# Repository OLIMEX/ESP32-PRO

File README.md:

# ESP32-PRO
Open-source hardware ESP32 IoT board with 4MB external RAM, 4MB external flash, LiPo charger, USB-OTG, external crypto engine option. The board uses PIC32 as USB-serial converter. 

Product page:

https://www.olimex.com/Products/IoT/ESP32/ESP32-PRO/open-source-hardware

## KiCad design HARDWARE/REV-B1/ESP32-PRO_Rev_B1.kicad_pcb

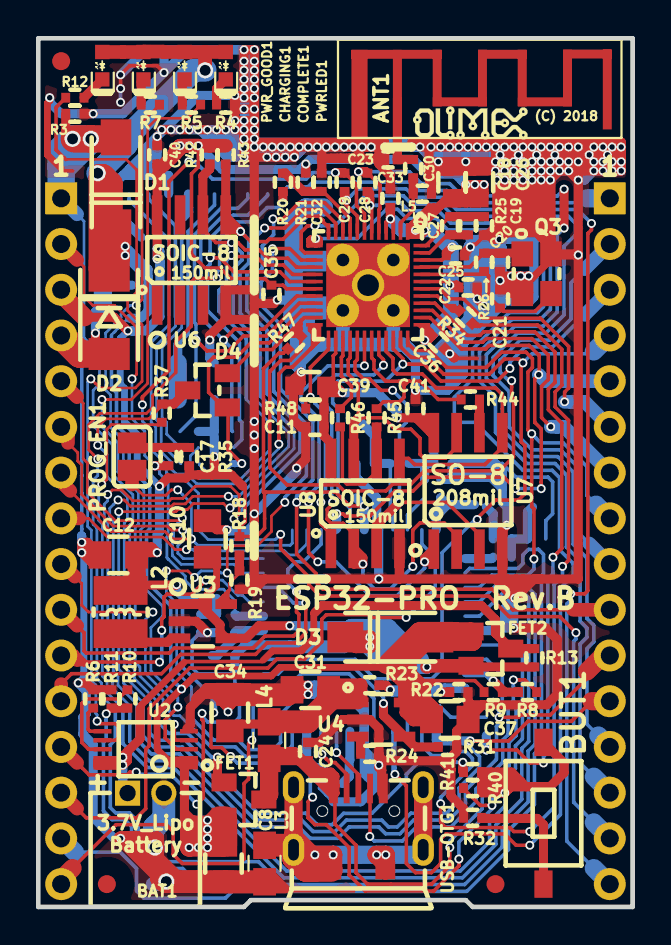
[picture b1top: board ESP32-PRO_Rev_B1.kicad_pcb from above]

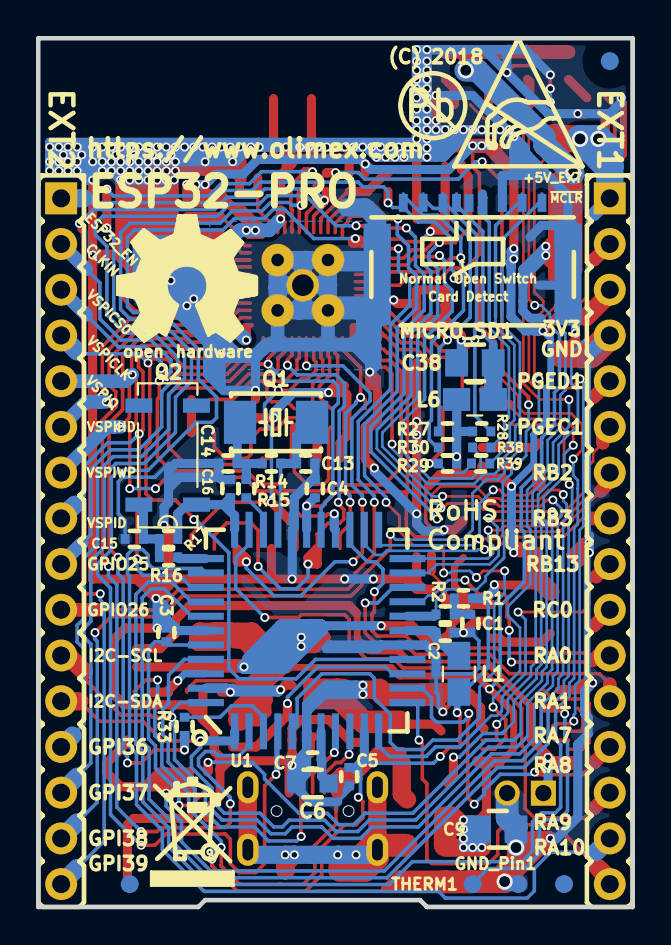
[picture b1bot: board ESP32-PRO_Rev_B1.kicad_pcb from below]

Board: 2 copper layers, 33.0 x 48.3 mm, 132 parts (40 on the bottom side), 104 nets.

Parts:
ANT1: WIFI_ANT; BT_Antenna_Inverted_1ANT_2GND
BAT1: DW02R; LIPO_BAT-CON2DW02R
BUT1: T1107A(6x3,8x2,5MM)
C1, C2, C3, C4, C5, C7, C11, C17, C22, C24, C32, C33, C35, C36, C41: 100nF/10V/10%/X5R/C0402; C_0402_5MIL_DWS
C6: 22uF/6.3V/20%/X5R/C0603; C_0603_5MIL_DWS
C8, C9, C10, C12, C31, C34, C37, C38: 47uF/6.3V/20%/X5R/C0805; C_0805_5MIL_DWS
C13, C14, C15, C16, C25: 33pF/50V/5%/COG/C0402; C_0402_5MIL_DWS
C18, C26, C39: 1uF/10V/10%/X5R/C0603; C_0603_5MIL_DWS
C19: 10nF/50V/10%/X7R/C0402; C_0402_5MIL_DWS
C20, C21: 22pF/50V/5%/COG/C0402; C_0402_5MIL_DWS
C23: 2.4pF/50V/±0.25pF/COG/C0402(Murata_Electronics/GR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; C_0402_5MIL_DWS
C27: 3.3nF/50V/10%/X7R/C0402; C_0402_5MIL_DWS
C28, C29: 270pF/50V/5%/COG/C0402; C_0402_5MIL_DWS
C30: 2.4nH/±0.1nH/220mA/300mR/L0402(Murata_Electronics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; C_0402_5MIL_DWS
C40: NA(100nF/10V/10%/X5R/C0402); C_0402_5MIL_DWS
CHARGING1: LED/YELLOW/0603; LED_0603_KA
COMPLETE1: LED/GREEN/0603; LED_0603_KA
D1, D3: 1N5822/SS34/SMA; SMA-KA
D2: SMBJ6.0A(DO-214AA); DO214AA_1(K)-2(A)
D4: BAT54C(SOT23-3); SOT23-3
EXT1, EXT2: NS(HN1x16); HN1x16
FET1, FET2: WPM2015-3/TR(SOT-23); SOT23
FID1, FID2, FID3, FID4, FID5, FID6: Fiducial; Fiducial1x3
GND_Pin1: TESTPAD; TESTPAD_40-ROUND
L1, L3, L4, L6: FB0805/600R/2A; L_0805_5MIL_DWS
L2: 2.2uH/1.5A/DCR<0.1R/CD32; CD32
L5: 4.7pF/50V/±0.1pF/COG/C0402(Murata_Electronics/GRM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; L_0402_5MIL_DWS
MICRO_SD1: TFC-9P-1.7H(ATFFS150A01BR016); uSD(TFC-9P-1.xH(ATFFS150A01BR016))
PROG_EN1: Unsoldered; SJ
PWRLED1: LED/RED/0603; LED_0603_KA
PWR_GOOD1: LED/RED/0603; LED_0603_KA
Q1: Q8.0MHz/20pF/20ppm/2P/5.0x3.2mm; HCX-4S_2Pins_5.0x3.2mm
Q2: Q32.768KHz/12.5pF/20ppm/2P/SMD_1206; MC306-HS
Q3: Q40.000MHz/12pF/10ppm/4P/3.2x2.5x0.70mm(Harmony_E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; TSX-3.2x2.5mm_GND(3)
R1, R3, R11, R21, R22, R31, R35, R40, R47, R48: 10k/R0402; R_0402_5MIL_DWS
R2, R10, R19: 1.1k/1%/R0402; R_0402_5MIL_DWS
R4, R5, R6, R7, R12, R15, R16, R27, R28, R29, R30, R42, R43: 2.2k/R0402; R_0402_5MIL_DWS
R8, R20, R32, R33, R34, R37, R39: 220R/R0402; R_0402_5MIL_DWS
R9: NA(220R/R0402); R_0402_5MIL_DWS
R13, R41, R45: NA/R0402; R_0402_5MIL_DWS
R14: 1M/1%/R0402; R_0402_5MIL_DWS
R17: NA(10M/1%/R0402); R_0402_5MIL_DWS
R18, R23: 4.99k/1%/R0402; R_0402_5MIL_DWS
R24: 13k/1%/R0402; R_0402_5MIL_DWS
R25: 20k/1%/R0402; R_0402_5MIL_DWS
R26: NA(1M/1%/R0402); R_0402_5MIL_DWS
R38, R44, R46: 22R/R0402; R_0402_5MIL_DWS
Ref**: Val**; LOGO_ANTISTATIC_1
THERM1: TESTPAD; TESTPAD_40-ROUND
U1: PIC32MX270F256DT-I/PT(TQFP44_10x10x1mm); TQFP44
U2: MCP73833(MSOP10); MSOP-10_Pitch-0.5mm_3.00x3.00x1.00mm
U3: SY8089AAAC(SOT23-5); SOT-23-5
U4: SY6280AAC(SOT23-5); SOT-23-5
U5: ESP32-D0WDQ6(QFN48_6x6mm); QFN48-6x6mm-OLIMEX_V2
U6: NA(ATECC508A-SSHDA-T(SOIC-8_150mil)); SOIC-8_150mil
U7: MX25U3235FM2I-10G(SOIC-8_208mil); SO-8_208mil
U8: LY68S3200SLT(SOIC-8_150mil); SOIC-8_150mil
USB-OTG1: MISB-SWMM-5AB-LF(USB-OTG_MICRO); USB-MICRO_MISB-SWMM-5B_LF

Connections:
+1V8: C11.2, C39.1, C41.2, R48.2, U5.26, U7.8, U8.8
+3V3: C3.1, C4.1, C5.1, C12.1, C18.1, C22.1, C25.1, C26.1, C33.1, C35.1, C36.1, C40.2, EXT1.3, L1.1, L2.2, L6.1, R1.2, R18.2, R21.1, R27.1, R28.1, R29.1, R30.1, R35.2, R40.2, R42.1, R43.1, R47.2, U1.10, U1.28, U1.40, U5.1, U5.3, U5.4, U5.19, U5.37, U5.43, U5.46, U6.8
+5V: C8.1, C9.1, C37.1, CHARGING1.2, COMPLETE1.2, D1.1, D2.1, D3.2, FET1.2, FET2.1, PWRLED1.2, PWR_GOOD1.2, R9.2, U2.1, U2.2, U4.5
+5V_EXT: D1.2, EXT1.1, FET1.1, R3.1
/+5V_USB-OTG: C24.1, FET1.3, L4.1, R8.2, USB-OTG1.1
/D_Com: D4.3, R37.2, R41.1
/ESP32_EN: EXT2.1, R20.1, U1.37
/ESP32_GPI35/BUT1: BUT1.1, R40.1, R41.2, U5.11
/ESP32_GPI36: C28.1, EXT2.13, U5.5
/ESP32_GPI37: C28.2, EXT2.14, U5.6
/ESP32_GPI38: C29.1, EXT2.15, U5.7
/ESP32_GPI39: C29.2, EXT2.16, U5.8
/ESP32_GPIO0/CLKIN: D4.2, EXT2.2, R47.1, U5.23
/ESP32_GPIO1/U0TXD: R34.2, U5.41
/ESP32_GPIO2/HS2_DATA0: D4.1, R29.2, R39.1, U5.22
/ESP32_GPIO3/U0RXD: R33.2, U5.40
/ESP32_GPIO4/HS2_DATA1: MICRO_SD1.8, U5.24
/ESP32_GPIO6/SD_CLK: R44.1, R45.1, U5.31
/ESP32_GPIO7/SD_DATA0: U5.32, U7.2, U8.2
/ESP32_GPIO8/SD_DATA1: U5.33, U7.5, U8.5
/ESP32_GPIO9/SD_DATA2: U5.28, U7.7, U8.7
/ESP32_GPIO10/SD_DATA3: U5.29, U7.3, U8.3
/ESP32_GPIO11/SD_CMD: U5.30, U7.1
/ESP32_GPIO12/HS2_DATA2: MICRO_SD1.1, R30.2, U5.18
/ESP32_GPIO13/HS2_DATA3: MICRO_SD1.2, R27.2, U5.20
/ESP32_GPIO14/HS2_CLK: R38.1, U5.17
/ESP32_GPIO15/HS2_CMD: MICRO_SD1.3, R28.2, U5.21
/ESP32_GPIO16/PSRAM_CS#: R48.1, U5.25, U8.1
/ESP32_GPIO17/PSRAM_SCLK: R46.1, U5.27
/ESP32_GPIO21/VSPIHD: EXT2.6, U5.42
/ESP32_GPIO22/VSPIWP: EXT2.7, U5.39
/ESP32_GPIO25: EXT2.9, U5.14
/ESP32_GPIO26: EXT2.10, U5.15
/RA0: EXT1.11, U1.19
/RA1: EXT1.12, U1.20
/RA2/OSC1: C13.1, Q1.1, R14.1, U1.30
/RA3/OSC2: R15.1, U1.31
/RA4/SOSCO: R16.1, U1.34
/RA7: EXT1.13, U1.13
/RA8: EXT1.14, U1.32
/RA9: EXT1.15, U1.35
/RA10: EXT1.16, U1.12
/RB0/PGED1: EXT1.5, U1.21
/RB1/PGEC1: EXT1.6, U1.22
/RB2: EXT1.7, PROG_EN1.1, U1.23
/RB3: EXT1.8, U1.24
/RB4/SOSCI: C16.1, Q2.2, R17.1, U1.33
/RB5/USB-OTG_ID: U1.41, USB-OTG1.4
/RB7/USB-OTG_FAULT: R22.1, R23.1, U1.43
/RB8/SCL1(ESP32_GPIO27/I2C-SCL): EXT2.11, R42.2, U1.44, U5.16, U6.6
/RB9/SDA1(ESP32_GPIO32/I2C-SDA): EXT2.12, R43.2, U1.1, U5.12, U6.5
/RB10/USB-OTG_D+: U1.8, USB-OTG1.3
/RB11/USB-OTG_D-: U1.9, USB-OTG1.2
/RB13: EXT1.9, U1.11
/RB14/USB-OTG_EN(VBUSON): R31.2, U1.14, U4.4
/RB15/SCK2(ESP32_GPIO18/VSPICLK): EXT2.4, U1.15, U5.35
/RC0: EXT1.10, U1.25
/RC1/SDO2(ESP32_GPIO19/VSPIQ): EXT2.5, U1.26, U5.38
/RC2/~SS2~(ESP32_GPIO5/VSPICS0): EXT2.3, U1.27, U5.34
/RC3/SDI2(ESP32_GPIO23/VSPID): EXT2.8, U1.36, U5.36
/RC5/~DTR~(ESP32_PGM): R37.1, U1.38
/RC6/U1RXD(ESP32_PGM): R34.1, U1.2
/RC7/U1TXD(ESP32_PGM): R33.1, U1.3
/RC8/U2RX(ESP32_GPIO33/U2TXD): U1.4, U5.13
/RC9/U2TX(ESP32_GPI34/U2RXD): U1.5, U5.10
/STAT1: R7.2, U2.3
/STAT2: R5.2, U2.4
/~MCLR: C17.1, EXT1.2, R2.2, U1.18
GND: ANT1.2, BAT1.2, C1.2, C2.2, C3.2, C4.2, C5.2, C6.2, C7.2, C8.2, C9.2, C10.1, C11.1, C12.2, C13.2, C14.2, C15.2, C16.2, C18.2, C19.2, C20.2, C21.2, C22.2, C23.1, C24.2, C25.2, C26.2, C31.2, C32.2, C33.2, C34.2, C35.2, C36.2, C37.2, C38.2, C39.2, C40.1, C41.1, D2.2, EXT1.4, GND_Pin1.1, L3.2, L5.2, MICRO_SD1.6, MICRO_SD1.CH1, Q3.3, R3.2, R4.2, R6.2, R11.2, R19.2, R22.2, R24.1, R31.1, R32.2, U1.6, U1.16, U1.29, U1.39, U2.5, U3.2, U4.2, U5.49, U6.4, U7.4, U8.4, USB-OTG1.5
unnamed: ANT1.1, C23.2, C30.2
unnamed: BAT1.1, FET2.3, R13.1, U2.9, U2.10
unnamed: BUT1.2, R32.1
unnamed: C1.1, R1.1, R2.1
unnamed: C2.1, L1.2, U1.17
unnamed: C6.1, C7.1, U1.7
unnamed: C10.2, D3.1, FET2.2, R13.2, U3.1, U3.4
unnamed: C14.1, Q1.2, R14.2, R15.2
unnamed: C15.1, Q2.1, R16.2, R17.2
unnamed: C17.2, PROG_EN1.2, R35.1
unnamed: C19.1, C27.2, R25.1, U5.48
unnamed: C20.1, Q3.1, R26.1, U5.45
unnamed: C21.1, Q3.2, R26.2, U5.44
unnamed: C27.1, R25.2, U5.47
unnamed: C30.1, L5.1, U5.2
unnamed: C31.1, C34.1, L4.2, R23.2, U4.1
unnamed: C32.1, R20.2, R21.2, U5.9
unnamed: C38.1, L6.2, MICRO_SD1.4
unnamed: CHARGING1.1, R7.1
unnamed: COMPLETE1.1, R5.1
unnamed: L2.1, U3.3
unnamed: L3.1, USB-OTG1.0
unnamed: MICRO_SD1.5, R38.2
unnamed: MICRO_SD1.7, R39.2
unnamed: PWRLED1.1, R4.1
unnamed: PWR_GOOD1.1, R12.1
unnamed: R6.1, U2.6
unnamed: R8.1, R9.1, U1.42
unnamed: R10.1, U2.8
unnamed: R10.2, R11.1, THERM1.1
unnamed: R12.2, U2.7
unnamed: R18.1, R19.1, U3.5
unnamed: R24.2, U4.3
unnamed: R44.2, U7.6
unnamed: R45.2, R46.2, U8.6

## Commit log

2017-06-21 ESP32-PRO schematic
2018-08-02 Update
    added rev B
2018-11-05 Update
    Arduino IDE demos
2019-01-28 Added readme
2020-05-05 update
    added bootloader
2020-09-01 Update
    revision B1 added
2021-12-02 Update
    Added bootloader + bridge binary
